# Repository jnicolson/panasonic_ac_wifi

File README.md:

# Panasonic Wifi Module

This is a hardware module designed to plug into the CN-CNT connector on compatible Panasonic Airconditing Units

This is designed to run the esphome-panasonic-ac ESPHome library created by DomiStyle (https://github.com/DomiStyle/esphome-panasonic-ac) and all credit for the software goes to DomiStyle and other contributors.  

A cable with a 5 pin JST PA connector on one end and a 4 pin Molex PicoBlade on the other is required.  The 12V from the CN-CNT connector is unused so is not connected.  You can buy 4 pin pre-crimped PicoBlade cables from the likes of Adafruit - crimping tiny connectors can be challenging so buying a pre-crimped tail and soldering it to longer wires with a JST PA connector on the other end is a good option.

Programming is done using a 6 pin programmer.  Any programmer which adheres to the ESPFlash convention should work.  A programmer designed by myself is available at https://go.jmn.id.au/espprog but there are others (e.g. [SuperHouse ESPF](https://github.com/SuperHouse/ESPF)).  Alternatively any serial adapter can be used, but the ESP32 will need to be put into boot mode manually by pulling GPIO0 to ground during startup.

The smallest component is the 0603 capacitors and resistors so with a steady hand it's not too difficult assembling by hand and reflowing with a toaster oven, frypan or similar.  Using a solder paste stencil is easier but it wouldn't be too hard to dispense the solder manually too.

This was developed in KiCAD 5.99 so the latest nightly build should be used until KiCAD 6 is formally released.

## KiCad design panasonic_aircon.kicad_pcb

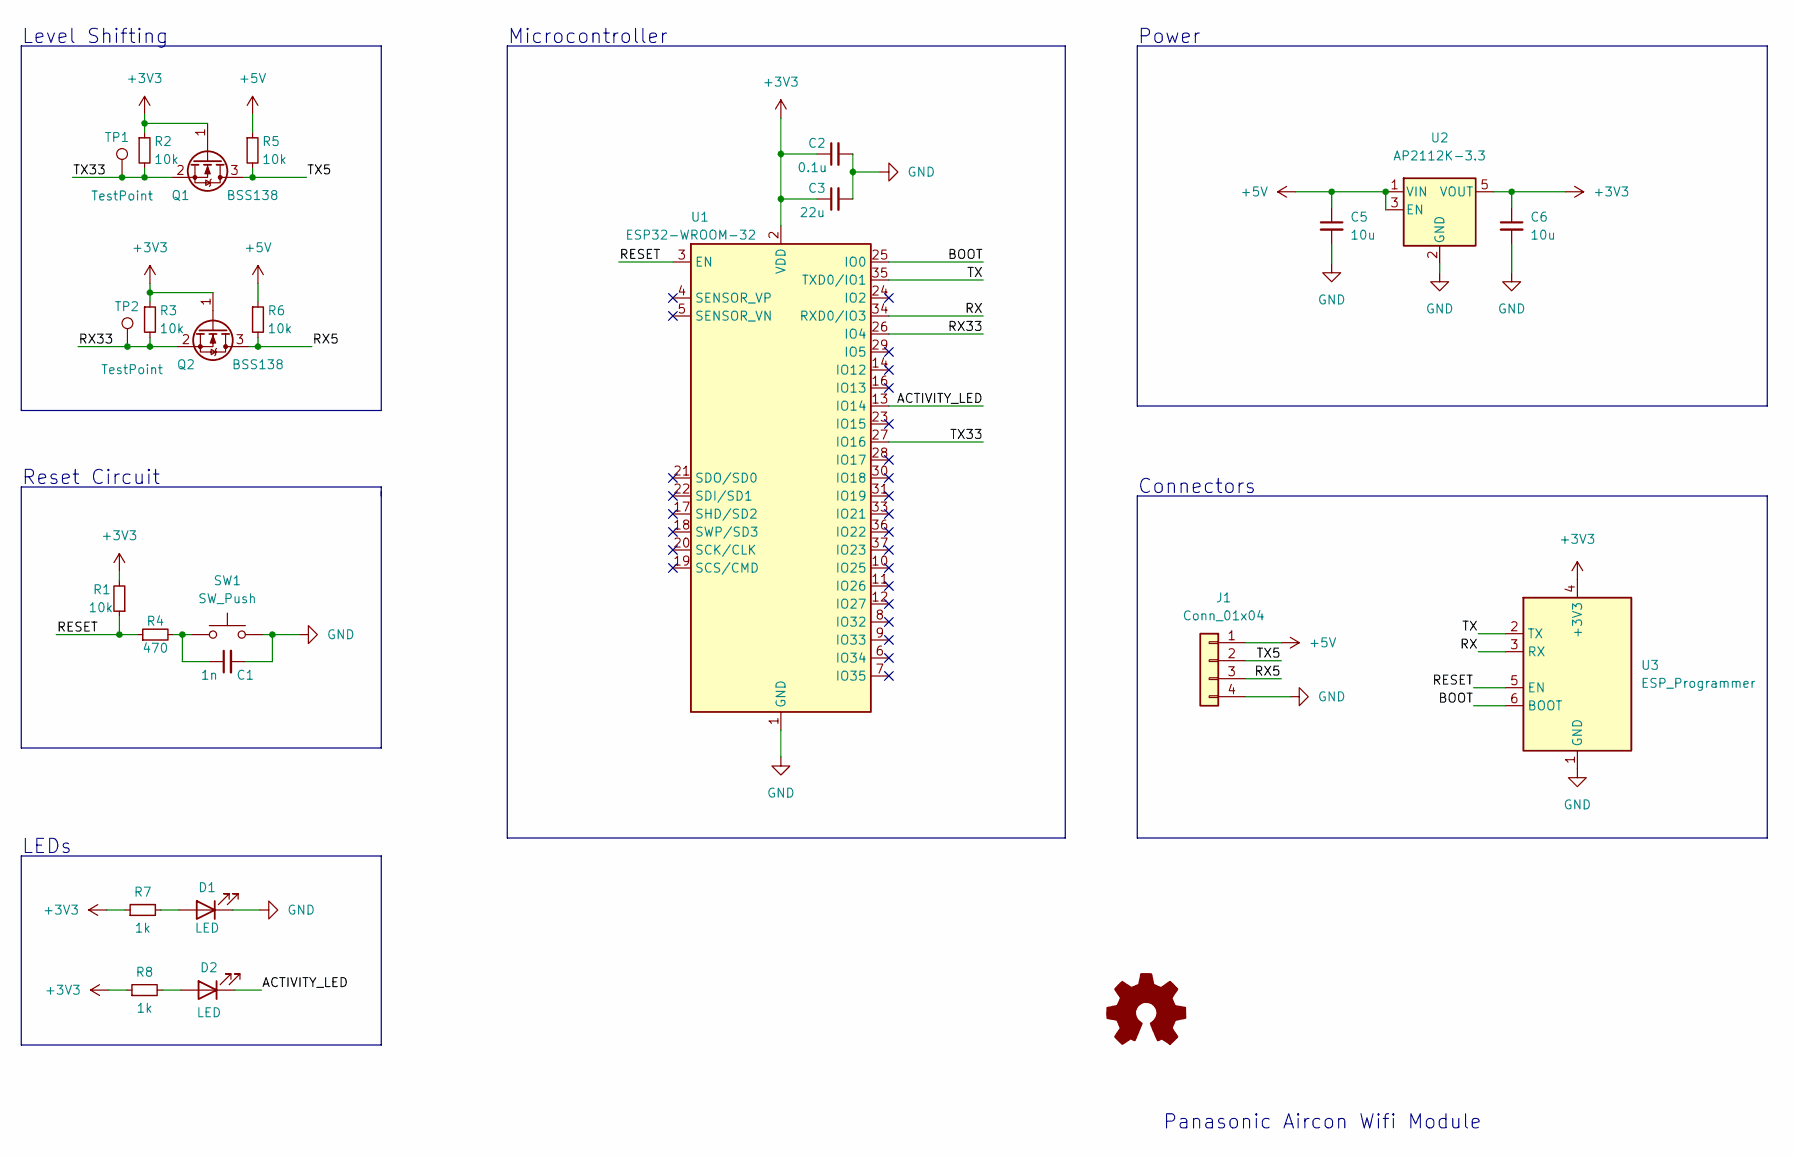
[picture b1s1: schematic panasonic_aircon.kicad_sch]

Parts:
C1: 1n; C_0603_1608Metric
C2: 0.1u; C_0603_1608Metric
C3: 22u; C_0805_2012Metric
C5, C6: 10u; C_0603_1608Metric
D1, D2: LED; LED_0603_1608Metric
J1: Conn_01x04; Molex_PicoBlade_53048-0410_1x04_P1.25mm_Horizontal
Q1, Q2: BSS138; SOT-23
R1, R2, R3, R5, R6: 10k; R_0603_1608Metric
R4: 470; R_0603_1608Metric
R7, R8: 1k; R_0603_1608Metric
SW1: SW_Push; SW_SPST_TS_1101_X_X
TP1, TP2: TestPoint; TestPoint_Pad_D1.5mm
U1: ESP32-WROOM-32
U2: AP2112K-3.3; SOT-23-5
U3: ESP_Programmer; PinHeader_1x06_P2.54mm_Vertical

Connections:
+3V3: C2.1, C3.1, C6.1, Q1.1 (G), Q2.1 (G), R1.2, R2.1, R3.1, R7.1, R8.1, U1.2 (VDD), U2.5 (VOUT), U3.4 (+3V3)
+5V: C5.1, J1.1, R5.1, R6.1, U2.1 (VIN), U2.3 (EN)
/ACTIVITY_LED: D2.1 (K), U1.13 (IO14)
/BOOT: U1.25 (IO0), U3.6 (BOOT)
/RESET: R1.1, R4.1, U1.3 (EN), U3.5 (EN)
/RX: U1.34 (RXD0/IO3), U3.3 (RX)
/RX5: J1.3, Q2.3 (D), R6.2
/RX33: Q2.2 (S), R3.2, TP2.1, U1.26 (IO4)
/TX: U1.35 (TXD0/IO1), U3.2 (TX)
/TX5: J1.2, Q1.3 (D), R5.2
/TX33: Q1.2 (S), R2.2, TP1.1, U1.27 (IO16)
GND: C1.2, C2.2, C3.2, C5.2, C6.2, D1.1 (K), J1.4, SW1.2, U1.1 (GND), U1.15 (GND), U1.38 (GND), U1.39 (GND), U2.2 (GND), U3.1 (GND)
unnamed: C1.1, R4.2, SW1.1
unnamed: D1.2 (A), R7.2
unnamed: D2.2 (A), R8.2

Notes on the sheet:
Level Shifting
Reset Circuit
LEDs
Microcontroller
Power
Connectors
Panasonic Aircon Wifi Module

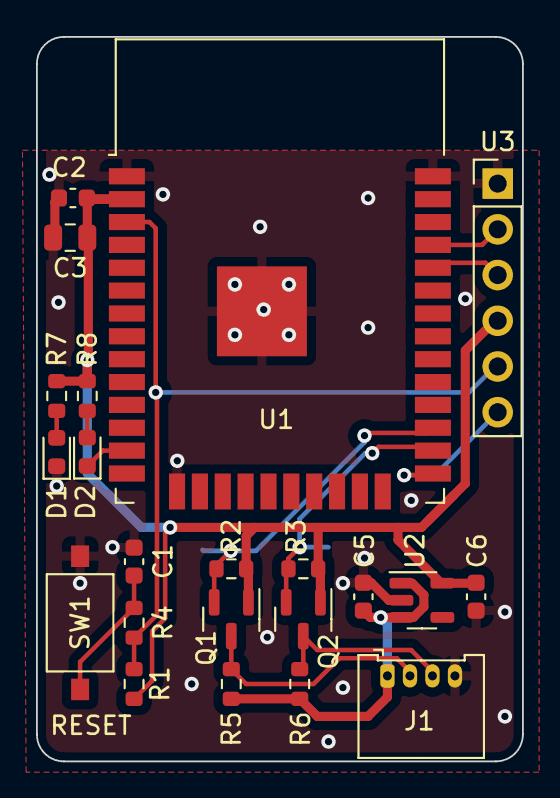
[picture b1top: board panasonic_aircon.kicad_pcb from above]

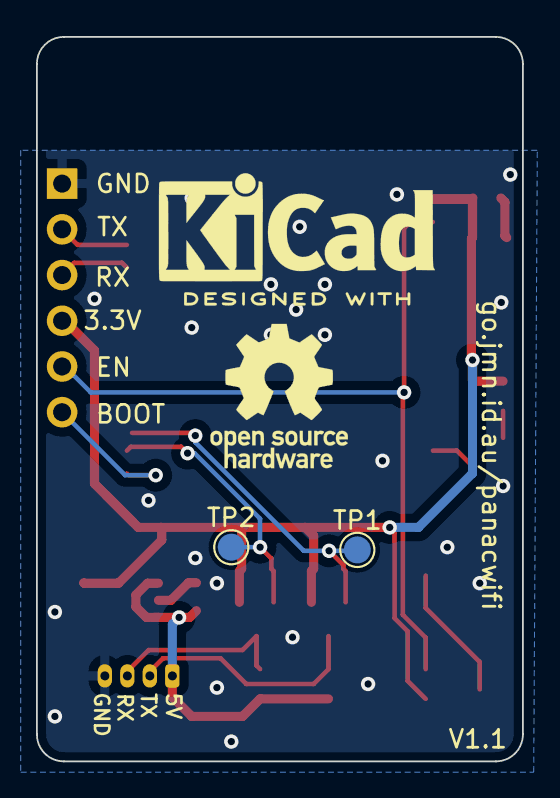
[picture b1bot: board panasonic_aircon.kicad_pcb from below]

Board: 2 copper layers, 27.0 x 40.2 mm, 24 parts (2 on the bottom side), 15 nets.

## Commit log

2021-10-04 Added gitignore
2021-10-04 Straight to Revision 1.1 - forgot to create repository before
2021-11-11 Cleanup Schematic layout, label each section
2021-11-11 Small update to edge of board
2021-11-11 Add schematic PDF document
2021-11-11 Update README and add image of finished board
2021-11-11 Added note about pre-crimped picoblade tails
